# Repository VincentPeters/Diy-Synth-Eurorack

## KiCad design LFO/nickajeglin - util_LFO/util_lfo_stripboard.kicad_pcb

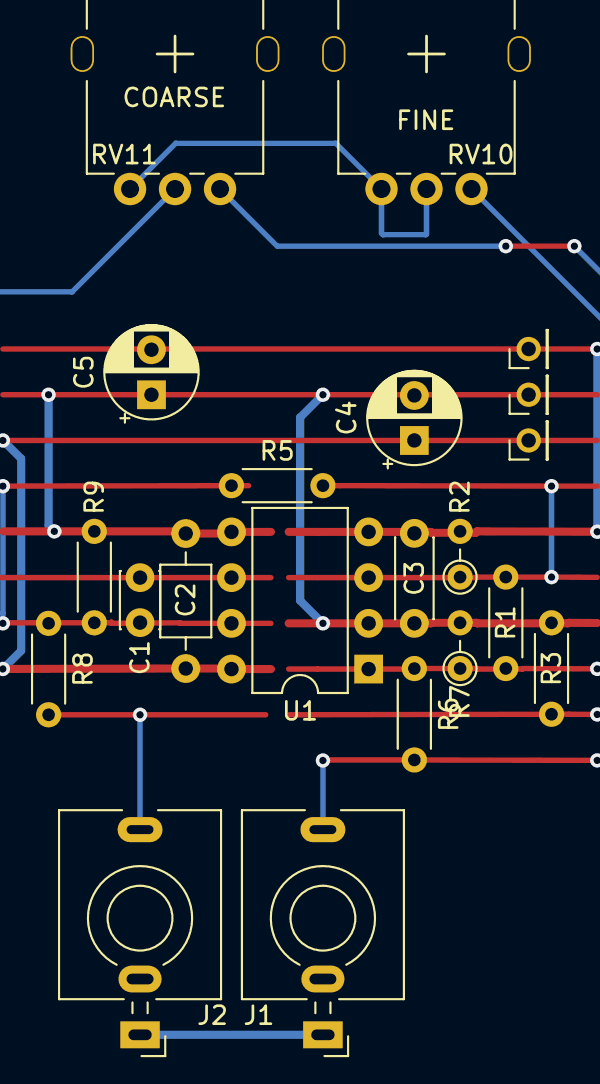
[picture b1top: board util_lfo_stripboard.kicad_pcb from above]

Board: 2 copper layers, 21 parts (0 on the bottom side), 11 nets.

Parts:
C1: 3300pF; C_Disc_D3.0mm_W2.0mm_P2.50mm
C2: 0.1uF; C_Axial_L3.8mm_D2.6mm_P7.50mm_Horizontal
C3: 0.1uF; C_Disc_D4.3mm_W1.9mm_P5.00mm
C4, C5: 10uF; CP_Radial_D5.0mm_P2.50mm
J1: SQR; 3.5mm_tip_switch_thonkiconn
J2: TRI; 3.5mm_tip_switch_thonkiconn
J4: +12; PinHeader_1x01_P2.00mm_Vertical
J5: GND; PinHeader_1x01_P2.00mm_Vertical
J6: -12; PinHeader_1x01_P2.00mm_Vertical
R1: 200K; R_Axial_DIN0204_L3.6mm_D1.6mm_P5.08mm_Horizontal
R2: 5M; R_Axial_DIN0204_L3.6mm_D1.6mm_P2.54mm_Vertical
R3: 220R; R_Axial_DIN0204_L3.6mm_D1.6mm_P5.08mm_Horizontal
R5: 100K; R_Axial_DIN0204_L3.6mm_D1.6mm_P5.08mm_Horizontal
R6, R9: 10K; R_Axial_DIN0204_L3.6mm_D1.6mm_P5.08mm_Horizontal
R7: 4.7K; R_Axial_DIN0204_L3.6mm_D1.6mm_P2.54mm_Vertical
R8: 2K; R_Axial_DIN0204_L3.6mm_D1.6mm_P5.08mm_Horizontal
RV10, RV11: B1M; Potentiometer_Thonk_Alpha_9mm_Vertical
U1: TL072; DIP-8_W7.62mm

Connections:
+12v: C2.1, C4.1, J4.1, U1.8
-12V: C3.2, C5.2, J6.1, R2.2, U1.4
GND: C2.2, C3.1, C4.2, C5.1, J1.S, J2.S, J5.1, R3.1, R7.2, R9.2, U1.2, U1.5
unnamed: C1.1, RV11.2, U1.6
unnamed: C1.2, R5.1, R8.1, R9.1, U1.7
unnamed: J1.T, R6.2
unnamed: J2.T, R8.2
unnamed: R1.1, R6.1, R7.1, RV10.1, U1.1
unnamed: R1.2, R2.1, R5.2, U1.3
unnamed: R3.2, RV11.1
unnamed: RV10.2, RV10.3, RV11.3

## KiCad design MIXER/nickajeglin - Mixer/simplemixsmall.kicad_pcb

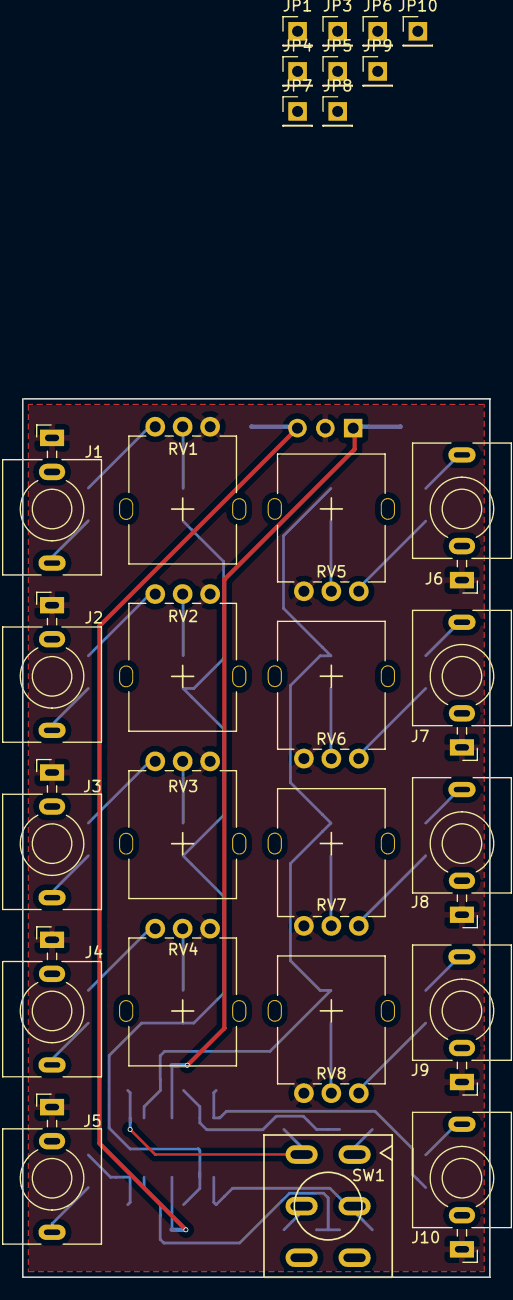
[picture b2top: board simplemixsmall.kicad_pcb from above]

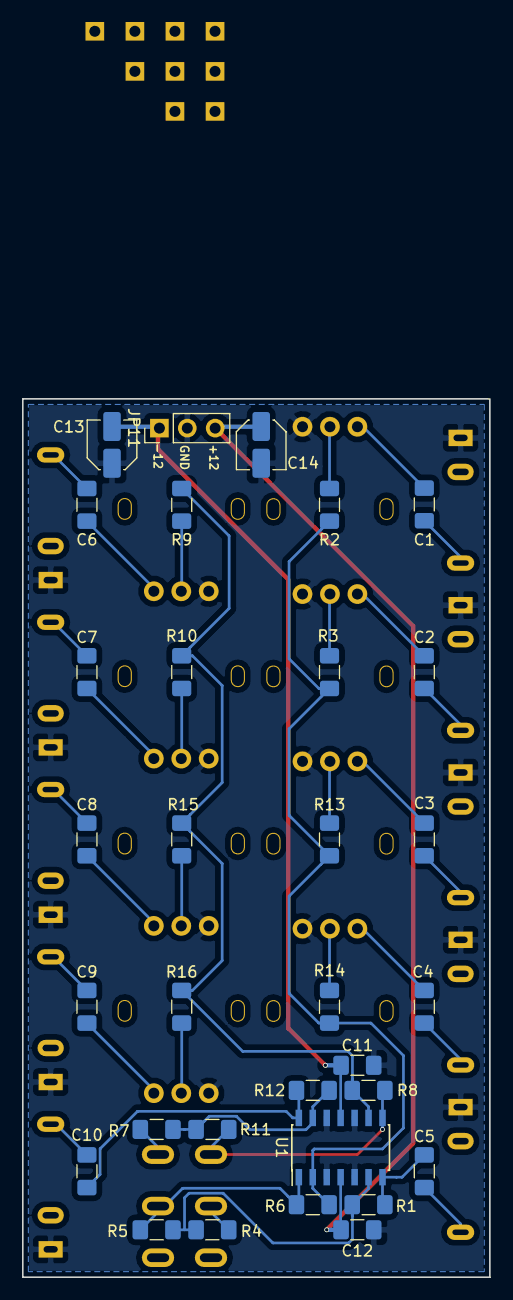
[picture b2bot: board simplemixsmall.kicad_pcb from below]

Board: 2 copper layers, 42.5 x 80.0 mm, 60 parts (32 on the bottom side), 39 nets.

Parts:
C1, C2, C3, C4, C6, C7, C8, C9, C11, C12: 0.1uF; C_1206_3216Metric_Pad1.42x1.75mm_HandSolder
C5, C10: 2uF; C_1206_3216Metric_Pad1.42x1.75mm_HandSolder
C13, C14: 10uF; C_Elec_4x5.4
J1: IN1; 3.5mm_tip_switch_thonkiconn
J2: IN2; 3.5mm_tip_switch_thonkiconn
J3: IN3; 3.5mm_tip_switch_thonkiconn
J4: IN4; 3.5mm_tip_switch_thonkiconn
J5: OUT1; 3.5mm_tip_switch_thonkiconn
J6: IN5; 3.5mm_tip_switch_thonkiconn
J7: IN6; 3.5mm_tip_switch_thonkiconn
J8: IN7; 3.5mm_tip_switch_thonkiconn
J9: IN8; 3.5mm_tip_switch_thonkiconn
J10: OUT2; 3.5mm_tip_switch_thonkiconn
JP1: IN1; PinHeader_1x01_P2.54mm_Vertical
JP3: IN3; PinHeader_1x01_P2.54mm_Vertical
JP4: IN4; PinHeader_1x01_P2.54mm_Vertical
JP5: OUT1; PinHeader_1x01_P2.54mm_Vertical
JP6: IN5; PinHeader_1x01_P2.54mm_Vertical
JP7: IN6; PinHeader_1x01_P2.54mm_Vertical
JP8: IN7; PinHeader_1x01_P2.54mm_Vertical
JP9: IN8; PinHeader_1x01_P2.54mm_Vertical
JP10: OUT2; PinHeader_1x01_P2.54mm_Vertical
JP11: PWR CHAIN; PinHeader_1x03_P2.54mm_Vertical
R1, R4, R5, R6, R7, R8, R11, R12: 100K; R_1206_3216Metric_Pad1.42x1.75mm_HandSolder
R2, R3, R9, R10, R13, R14, R15, R16: 33K; R_1206_3216Metric_Pad1.42x1.75mm_HandSolder
RV1, RV2, RV3, RV4, RV5, RV6, RV7, RV8: 100K; Potentiometer_Thonk_Alpha_9mm_Vertical
SW1: CONFIG; toggle_switch_mini_DPDT
U1: TL074; SOIC-14_3.9x8.7mm_P1.27mm

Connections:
+12V: C12.1, C14.1, JP11.3, U1.4
-12V: C11.1, C13.2, JP11.1, U1.11
GND: C11.2, C12.2, C13.1, C14.2, J1.S, J2.S, J3.S, J4.S, J5.S, J6.S, J7.S, J8.S, J9.S, J10.S, JP11.2, RV1.3, RV2.3, RV3.3, RV4.3, RV5.3, RV6.3, RV7.3, RV8.3, U1.3, U1.5, U1.10, U1.12
unnamed: C1.1, J1.T, JP1.1
unnamed: C1.2, RV1.1
unnamed: C2.1, J2.T
unnamed: C2.2, RV2.1
unnamed: C3.1, J3.T, JP3.1
unnamed: C3.2, RV3.1
unnamed: C4.1, J4.T, JP4.1
unnamed: C4.2, RV4.1
unnamed: C5.1, R1.1, U1.7
unnamed: C5.2, J5.T, JP5.1
unnamed: C6.1, J6.T, JP6.1
unnamed: C6.2, RV5.1
unnamed: C7.1, J7.T, JP7.1
unnamed: C7.2, RV6.1
unnamed: C8.1, J8.T, JP8.1
unnamed: C8.2, RV7.1
unnamed: C9.1, J9.T, JP9.1
unnamed: C9.2, RV8.1
unnamed: C10.1, R12.1, U1.14
unnamed: C10.2, J10.T, JP10.1
unnamed: R1.2, R4.2, R5.2, U1.6
unnamed: R2.2, RV1.2
unnamed: R3.2, RV2.2
unnamed: R4.1, SW1.5
unnamed: R5.1, R6.1, SW1.2, U1.1
unnamed: R7.2, SW1.1
unnamed: R9.2, RV5.2
unnamed: R8.2, R9.1, R10.1, R15.1, R16.1, U1.9
unnamed: R10.2, RV6.2
unnamed: R8.1, R11.1, SW1.4, U1.8
unnamed: R7.1, R11.2, R12.2, U1.13
unnamed: R2.1, R3.1, R6.2, R13.1, R14.1, U1.2
unnamed: R13.2, RV3.2
unnamed: R14.2, RV4.2
unnamed: R15.2, RV7.2
unnamed: R16.2, RV8.2
